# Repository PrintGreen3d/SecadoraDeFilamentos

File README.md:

# Estufa Secagem

A grande maioria dos polímeros são higroscópicos ou seja é uma característica de determinados materiais plásticos que diz respeito à capacidade de eles absorverem água. Na industria é uma pratica comum "secar" o material e quanto mais água absorvem, mais tempo permanecem no funil alimentador secador para que sejam desumidificados antes de serem utilizados.

# Versão Anteriores	

No desenvolvimento tive 2 versão a [primeira versão](https://github.com/PrintGreen3d/retiraUmidade-V0.1), usei uma caixa de papelão, secador de cabelo, lm35 e um arduino para fazer o controle de temperatura.

# Versão Atual	
Nesta versão reciclei uma estufa antiga de dentista. A mesma tem pelo menos 19 anos e não existe mais peças de reposição, as poucas que encontrei o preço foi fora do orçamento, decidi remover as peças antigas e instalar um lcd e controle de temperatura e tempo na estufa. 

## Pastas

O Projeto conta com 3 pastas

 - Codigo fonte do arduino;
 - Arquivos OpenSCAD do case do lcd;
 - Arquivos para confecção de uma placa de controle. 

## Componentes
- Arduino Uno/Nano
- Lm35
- Lcd 4 vias i2c
- rtc3231
- Potenciômetro 10k
- Botão

## Video 
O funcionamento atual pode ser visto neste link:

https://youtu.be/8OtH3Y8lwzA

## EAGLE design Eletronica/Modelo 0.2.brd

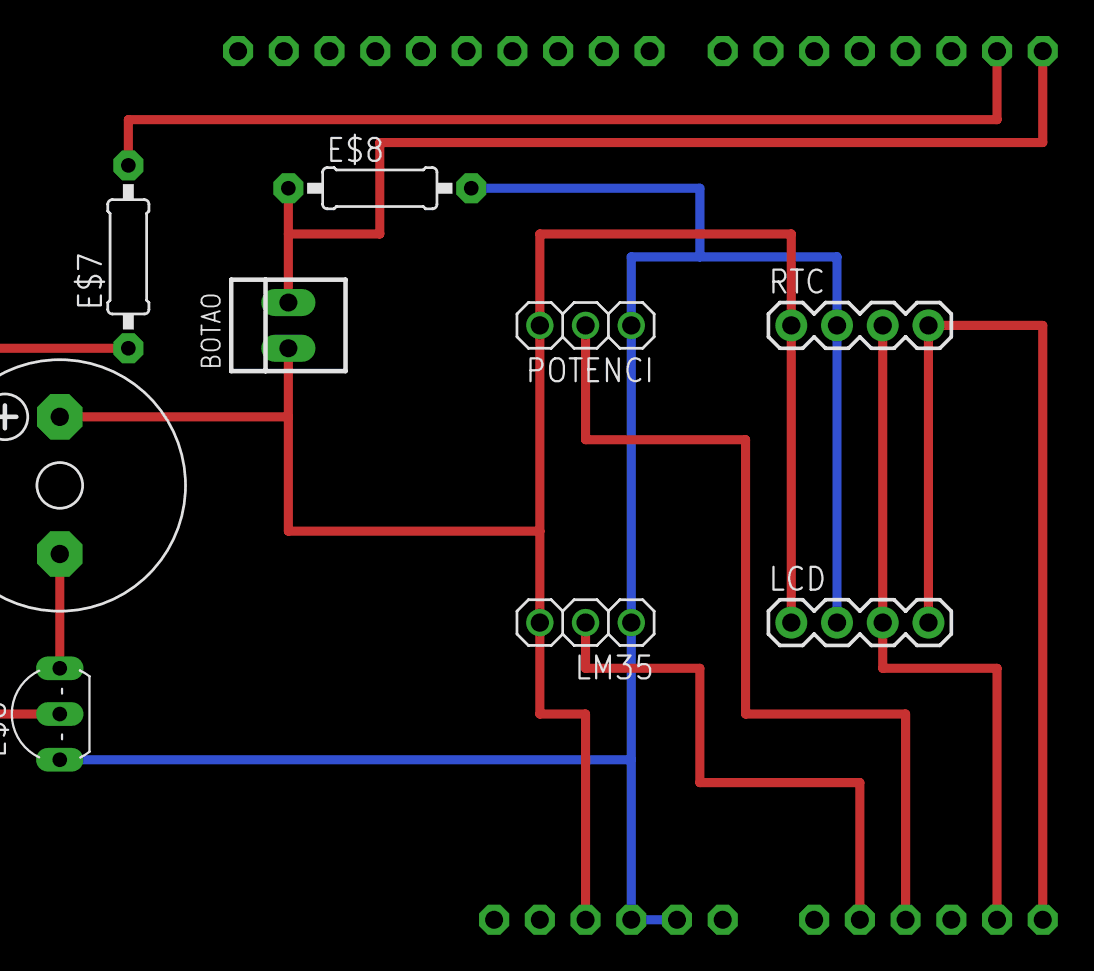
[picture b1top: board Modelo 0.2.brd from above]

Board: 2 copper layers, 10 parts (0 on the bottom side), 10 nets.

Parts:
BOTAO: 22-23-2021
E$1: ARDUINOR3-NOTEXT-NOIOREF
E$6: TO92-OVAL
E$7, E$8: 0207/10
E$9: F/CM12P
LCD: 1X04-BIG
LM35: 1X03
POTENCI: 1X03
RTC: 1X04-BIG

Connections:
S$1: E$1.A5, LCD.4, RTC.4
S$2: E$1.A4, LCD.3, RTC.3
S$3: E$1.GND1, E$1.GND2, E$6.1, E$8.2, LCD.2, LM35.1, POTENCI.1, RTC.2
S$4: BOTAO.1, E$1.5V, E$9.+, LCD.1, LM35.3, POTENCI.3, RTC.1
S$5: E$1.A2, POTENCI.2
S$6: E$1.A1, LM35.2
S$7: BOTAO.2, E$1.D0, E$8.1
S$8: E$6.3, E$9.-
S$9: E$1.D1, E$7.2
S$10: E$6.2, E$7.1

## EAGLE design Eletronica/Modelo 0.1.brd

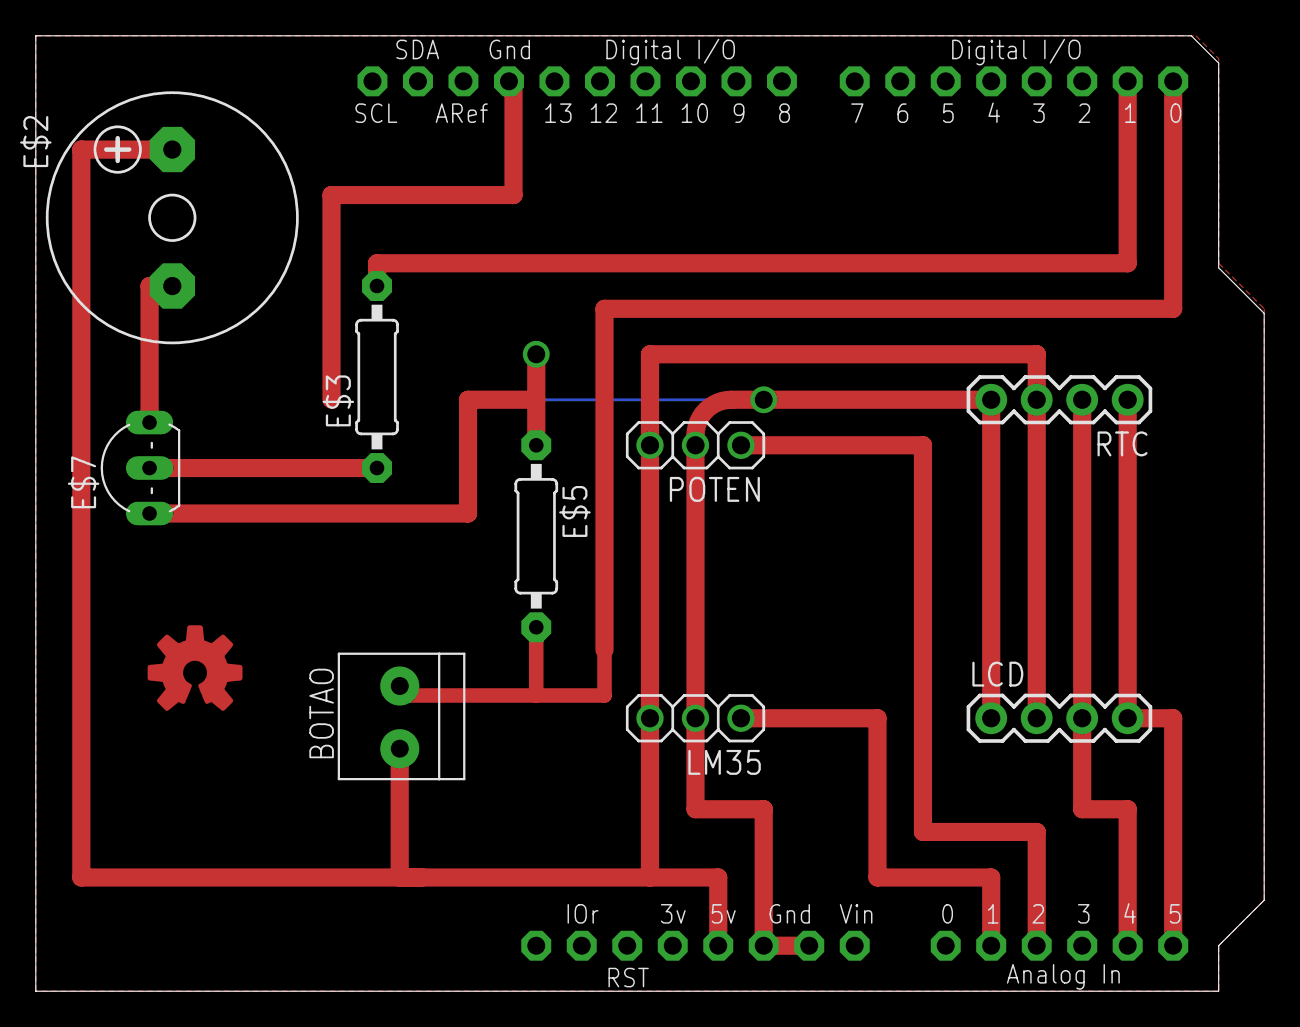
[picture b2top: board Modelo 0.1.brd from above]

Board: 2 copper layers, 68.6 x 53.3 mm, 11 parts (0 on the bottom side), 10 nets.

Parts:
BOTAO: 1X2-3.5MM
E$1: ARDUINOR3
E$2: F/CM12P
E$3, E$5: 0207/10
E$4: OSHWLOGO_TOP_0.2
E$7: TO92-EBC-OVAL
LCD: 1X04-BIG
LM35: 1X03
POTEN: 1X03
RTC: 1X04-BIG

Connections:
GND: E$1.GND1, E$1.GND2, E$5.1, E$7.E, LCD.1, LM35.2, POTEN.2, RTC.4
S$1: E$1.5V, LCD.2, LM35.3, POTEN.3, RTC.3
S$2: E$3.1, E$7.B
S$3: E$1.A1, LM35.1
S$4: E$1.D0, E$5.2
S$5: E$1.D1, E$3.2
S$6: E$1.A2, POTEN.1
S$7: E$1.A5, LCD.4, RTC.1
S$8: E$1.A4, LCD.3, RTC.2
S$9: E$2.-, E$7.C

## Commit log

2018-07-05 Primeira versão
2018-07-05 Alteração do README
2018-07-05 Alteração do README 2
2018-07-05 Alteração do README e remoção do video
2018-07-05 Alteração do codigo
2018-07-05 Subindo arquivo do arduino
2018-07-11 Ajuste de Hora e Data pelo LCD
2018-07-11 Removendo arquivo .ino repetido
2018-07-18 Correção de variaveis e de leitura do potenciometro
